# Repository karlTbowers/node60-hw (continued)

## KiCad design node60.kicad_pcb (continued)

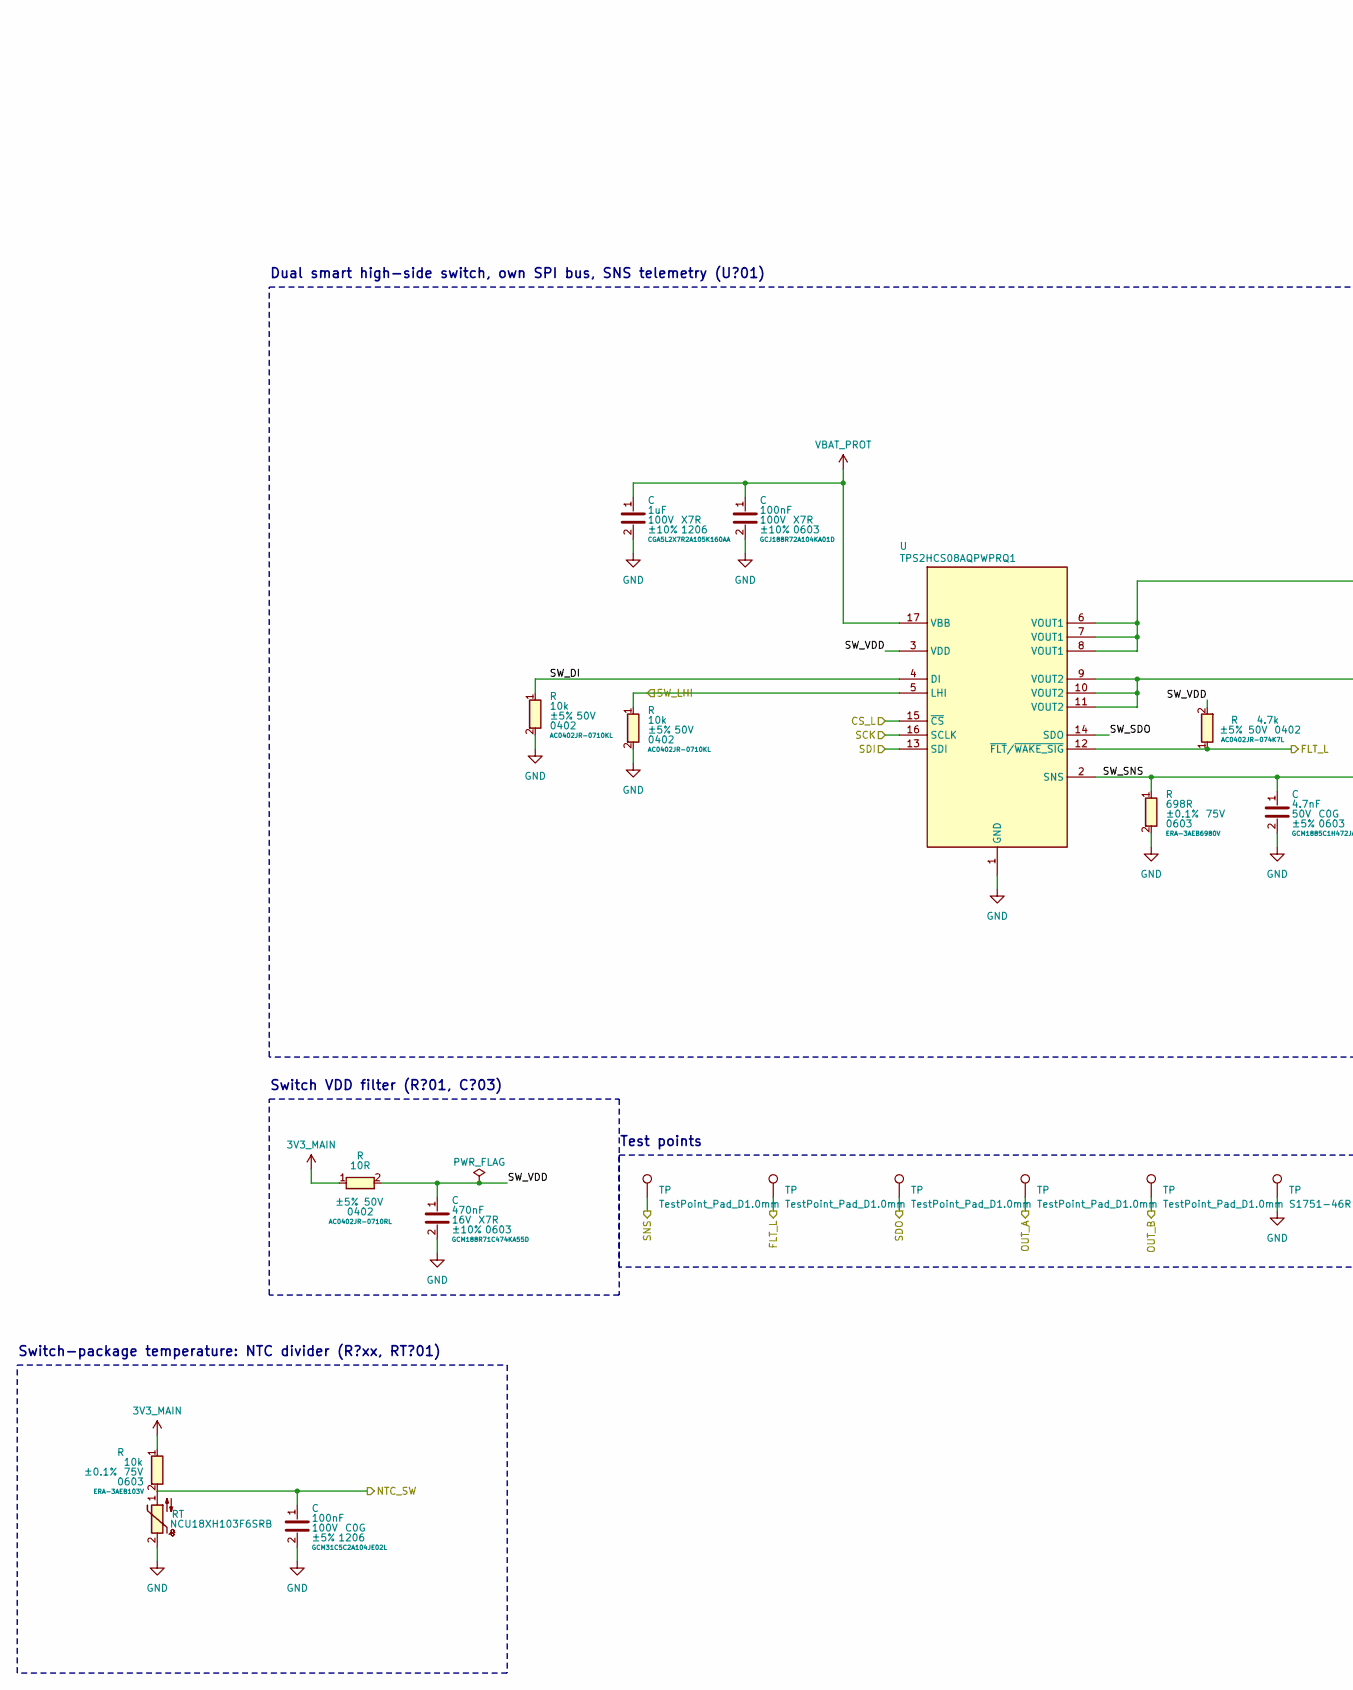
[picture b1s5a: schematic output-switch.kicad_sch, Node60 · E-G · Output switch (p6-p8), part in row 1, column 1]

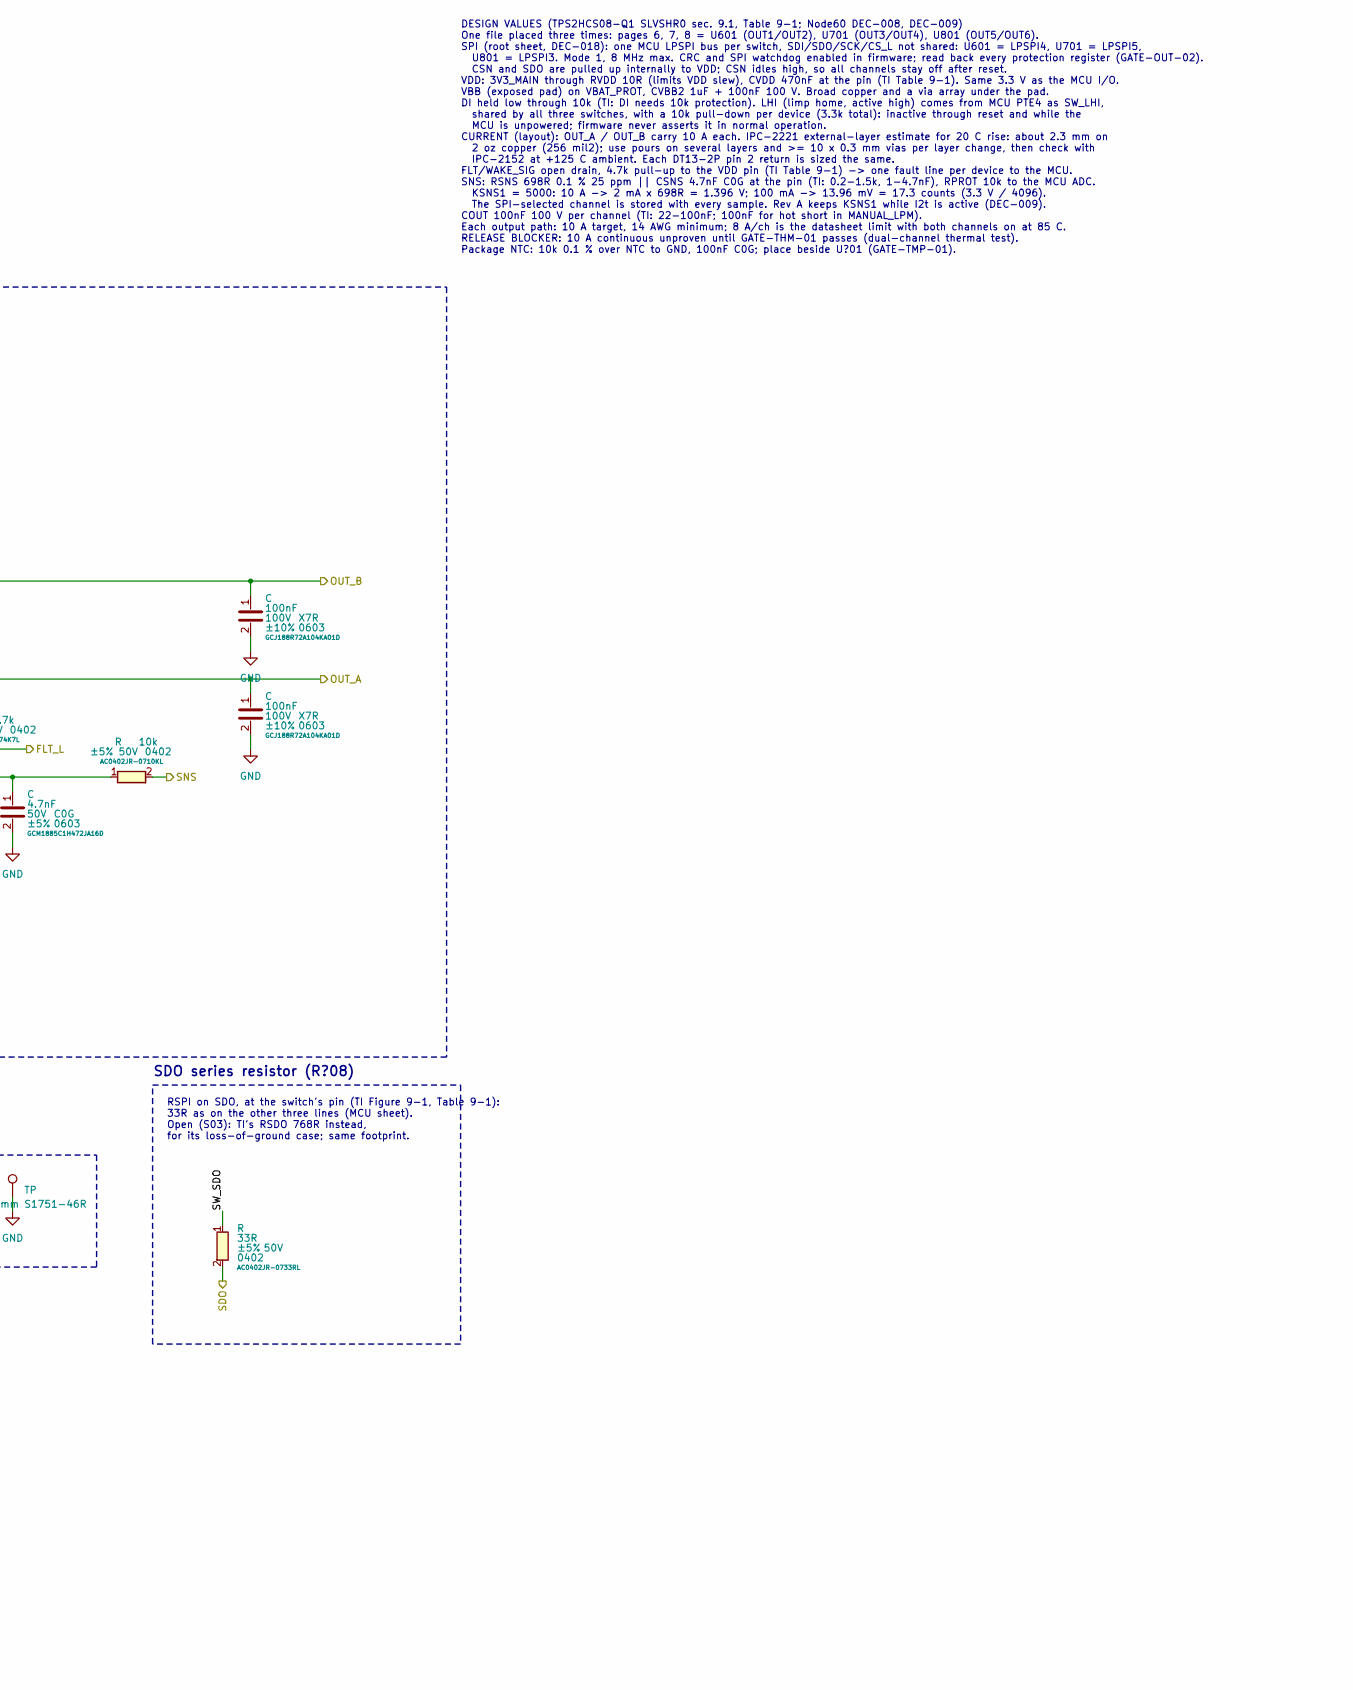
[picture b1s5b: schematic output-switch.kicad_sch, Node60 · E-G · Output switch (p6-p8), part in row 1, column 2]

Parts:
C: 100nF; C_0603_1608Metric; Voltage 100V; Tolerance ±10%; MPN GCJ188R72A104KA01D; DigiKey_PN 490-13420-1-ND
R: 10R; R_0402_1005Metric; Tolerance ±5%; Voltage 50V; MPN AC0402JR-0710RL; DigiKey_PN YAG3519CT-ND
RT: NCU18XH103F6SRB; R_NTC_0603_1608Metric_Pad0.7x0.7mm; MPN NCU18XH103F6SRB; DigiKey_PN 490-18139-1-ND
TP: TestPoint_Pad_D1.0mm; MPN TestPoint_Pad_D1.0mm
U: TPS2HCS08AQPWPRQ1; HTSSOP-16-1EP_4.4x5mm_P0.65mm_EP3.4x5mm_Mask2.78x3.313mm; MPN TPS2HCS08AQPWPRQ1; DigiKey_PN 296-TPS2HCS08AQPWPRQ1CT-ND

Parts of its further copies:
C601, C605, C606, C607, C701, C705, C706, C707, C801, C805, C806, C807: 100nF; C_0603_1608Metric; Voltage 100V; Tolerance ±10%; MPN GCJ188R72A104KA01D; DigiKey_PN 490-13420-1-ND
R601, R701, R801: 10R; R_0402_1005Metric; Tolerance ±5%; Voltage 50V; MPN AC0402JR-0710RL; DigiKey_PN YAG3519CT-ND
RT601, RT701, RT801: NCU18XH103F6SRB; R_NTC_0603_1608Metric_Pad0.7x0.7mm; MPN NCU18XH103F6SRB; DigiKey_PN 490-18139-1-ND
TP601, TP602, TP603, TP604, TP605, TP701, TP702, TP703, TP704, TP705, TP801, TP802, TP803, TP804, TP805: TestPoint_Pad_D1.0mm; MPN TestPoint_Pad_D1.0mm
U601, U701, U801: TPS2HCS08AQPWPRQ1; HTSSOP-16-1EP_4.4x5mm_P0.65mm_EP3.4x5mm_Mask2.78x3.313mm; MPN TPS2HCS08AQPWPRQ1; DigiKey_PN 296-TPS2HCS08AQPWPRQ1CT-ND

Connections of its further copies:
3V3_MAIN: R601.1, R701.1, R801.1; also elsewhere on the board
/NTC_SW1: C607.1, RT601.1; also elsewhere on the board
/NTC_SW2: C707.1, RT701.1; also elsewhere on the board
/NTC_SW3: C807.1, RT801.1; also elsewhere on the board
/OUT1: C606.1, TP604.1 (1_1), U601.9 (VOUT2), U601.10 (VOUT2), U601.11 (VOUT2); also elsewhere on the board
/OUT2: C605.1, TP605.1 (1_1), U601.6 (VOUT1), U601.7 (VOUT1), U601.8 (VOUT1); also elsewhere on the board
/OUT3: C706.1, TP704.1 (1_1), U701.9 (VOUT2), U701.10 (VOUT2), U701.11 (VOUT2); also elsewhere on the board
/OUT4: C705.1, TP705.1 (1_1), U701.6 (VOUT1), U701.7 (VOUT1), U701.8 (VOUT1); also elsewhere on the board
/OUT5: C806.1, TP804.1 (1_1), U801.9 (VOUT2), U801.10 (VOUT2), U801.11 (VOUT2); also elsewhere on the board
/OUT6: C805.1, TP805.1 (1_1), U801.6 (VOUT1), U801.7 (VOUT1), U801.8 (VOUT1); also elsewhere on the board
/Outputs 1-2/SW_DI: U601.4 (DI); also elsewhere on the board
/Outputs 1-2/SW_SDO: U601.14 (SDO); also elsewhere on the board
/Outputs 1-2/SW_SNS: U601.2 (SNS); also elsewhere on the board
/Outputs 1-2/SW_VDD: R601.2, U601.3 (VDD); also elsewhere on the board
/Outputs 3-4/SW_DI: U701.4 (DI); also elsewhere on the board
/Outputs 3-4/SW_SDO: U701.14 (SDO); also elsewhere on the board
/Outputs 3-4/SW_SNS: U701.2 (SNS); also elsewhere on the board
/Outputs 3-4/SW_VDD: R701.2, U701.3 (VDD); also elsewhere on the board
/Outputs 5-6/SW_DI: U801.4 (DI); also elsewhere on the board
/Outputs 5-6/SW_SDO: U801.14 (SDO); also elsewhere on the board
/Outputs 5-6/SW_SNS: U801.2 (SNS); also elsewhere on the board
/Outputs 5-6/SW_VDD: R801.2, U801.3 (VDD); also elsewhere on the board
/SPI3_SWITCH3_CS_L: U801.15 (~CS); also elsewhere on the board
/SPI3_SWITCH3_MISO: TP803.1 (1_1); also elsewhere on the board
/SPI3_SWITCH3_MOSI: U801.13 (SDI); also elsewhere on the board
/SPI3_SWITCH3_SCK: U801.16 (SCLK); also elsewhere on the board
/SPI4_SWITCH1_CS_L: U601.15 (~CS); also elsewhere on the board
/SPI4_SWITCH1_MISO: TP603.1 (1_1); also elsewhere on the board
/SPI4_SWITCH1_MOSI: U601.13 (SDI); also elsewhere on the board
/SPI4_SWITCH1_SCK: U601.16 (SCLK); also elsewhere on the board
/SPI5_SWITCH2_CS_L: U701.15 (~CS); also elsewhere on the board
/SPI5_SWITCH2_MISO: TP703.1 (1_1); also elsewhere on the board
/SPI5_SWITCH2_MOSI: U701.13 (SDI); also elsewhere on the board
/SPI5_SWITCH2_SCK: U701.16 (SCLK); also elsewhere on the board
/SW1_FLT_L: TP602.1 (1_1), U601.12 (~FLT/~WAKE_SIG); also elsewhere on the board
/SW1_SNS: TP601.1 (1_1); also elsewhere on the board
/SW2_FLT_L: TP702.1 (1_1), U701.12 (~FLT/~WAKE_SIG); also elsewhere on the board
/SW2_SNS: TP701.1 (1_1); also elsewhere on the board
/SW3_FLT_L: TP802.1 (1_1), U801.12 (~FLT/~WAKE_SIG); also elsewhere on the board
/SW3_SNS: TP801.1 (1_1); also elsewhere on the board
/SW_LHI: U601.5 (LHI), U701.5 (LHI), U801.5 (LHI); also elsewhere on the board
GND: C601.2, C605.2, C606.2, C607.2, C701.2, C705.2, C706.2, C707.2, C801.2, C805.2, C806.2, C807.2, RT601.2, RT701.2, RT801.2, U601.1 (GND), U701.1 (GND), U801.1 (GND); also elsewhere on the board
VBAT_PROT: C601.1, C701.1, C801.1, U601.17 (VBB), U701.17 (VBB), U801.17 (VBB); also elsewhere on the board

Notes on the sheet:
Dual smart high-side switch, own SPI bus, SNS telemetry (U?01)
Switch VDD filter (R?01, C?03)
Switch-package temperature: NTC divider (R?xx, RT?01)
Test points
DESIGN VALUES (TPS2HCS08-Q1 SLVSHR0 sec. 9.1, Table 9-1; Node60 DEC-008, DEC-009) One file placed three times: pages 6, 7, 8 = U601 (OUT1/OUT2), U701 (OUT3/OUT4), U801 (OUT5/OUT6). SPI (root sheet, DEC-018): one MCU LPSPI bus per switch, SDI/SDO/SCK/CS_L not shared: U601 = LPSPI4, U701 = LPSPI5, U8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
SDO series resistor (R?08)
RSPI on SDO, at the switch's pin (TI Figure 9-1, Table 9-1): 33R as on the other three lines (MCU sheet). Open (S03): TI's RSDO 768R instead, for its loss-of-ground case; same footprint.

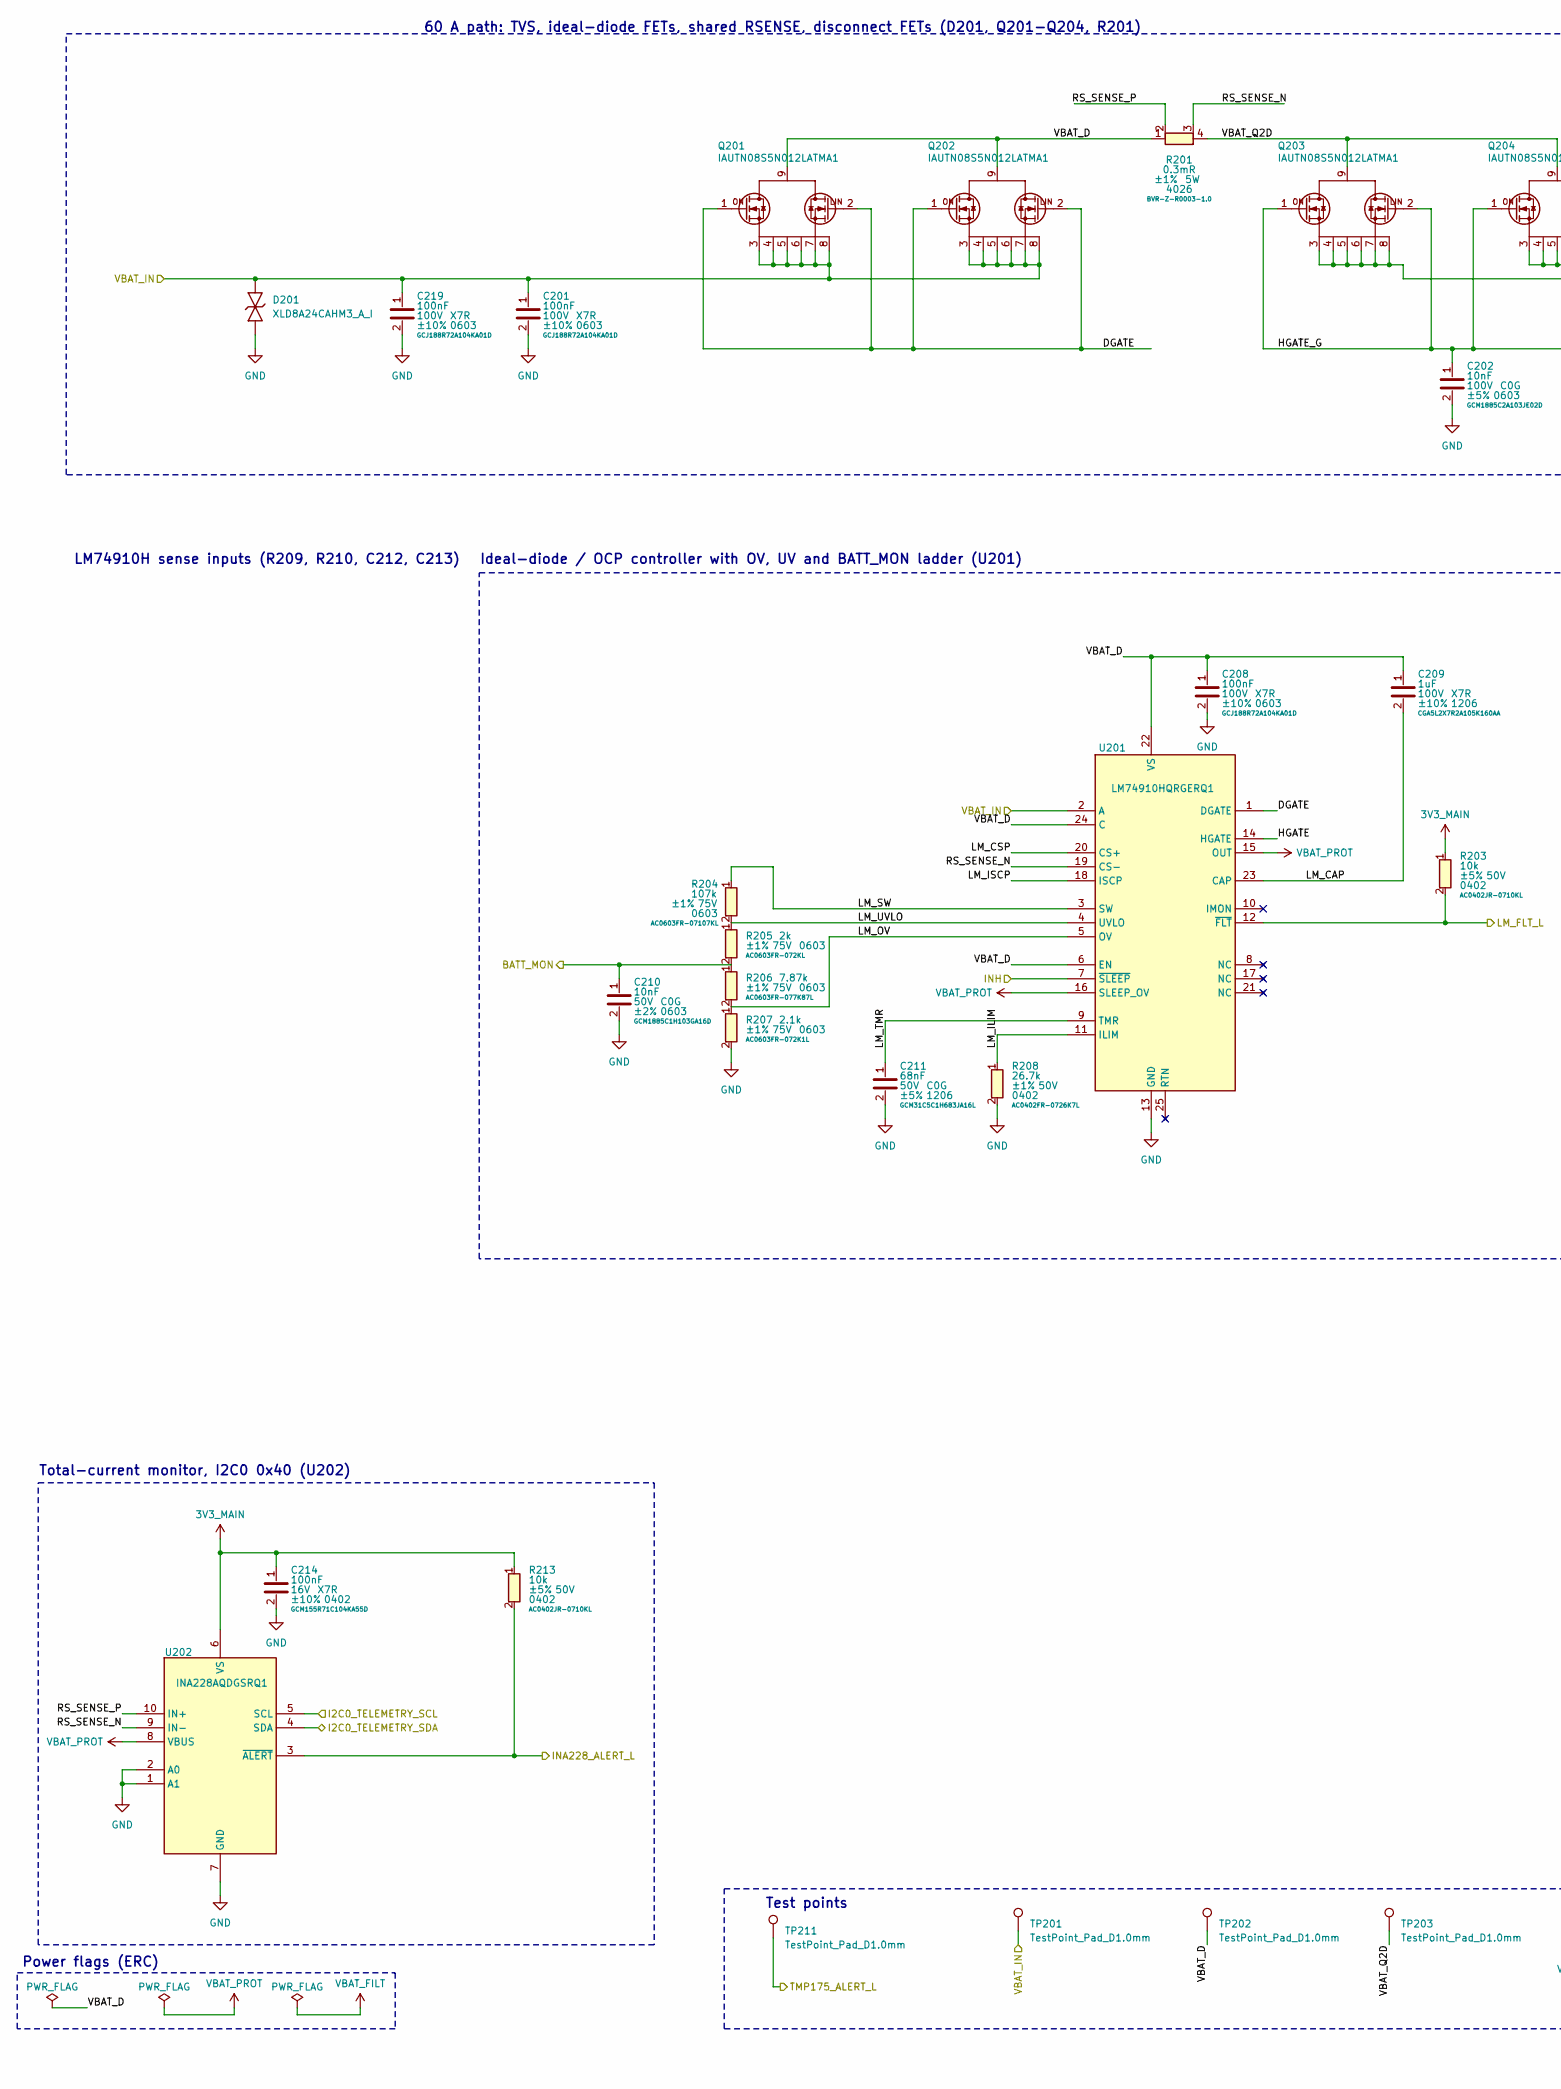
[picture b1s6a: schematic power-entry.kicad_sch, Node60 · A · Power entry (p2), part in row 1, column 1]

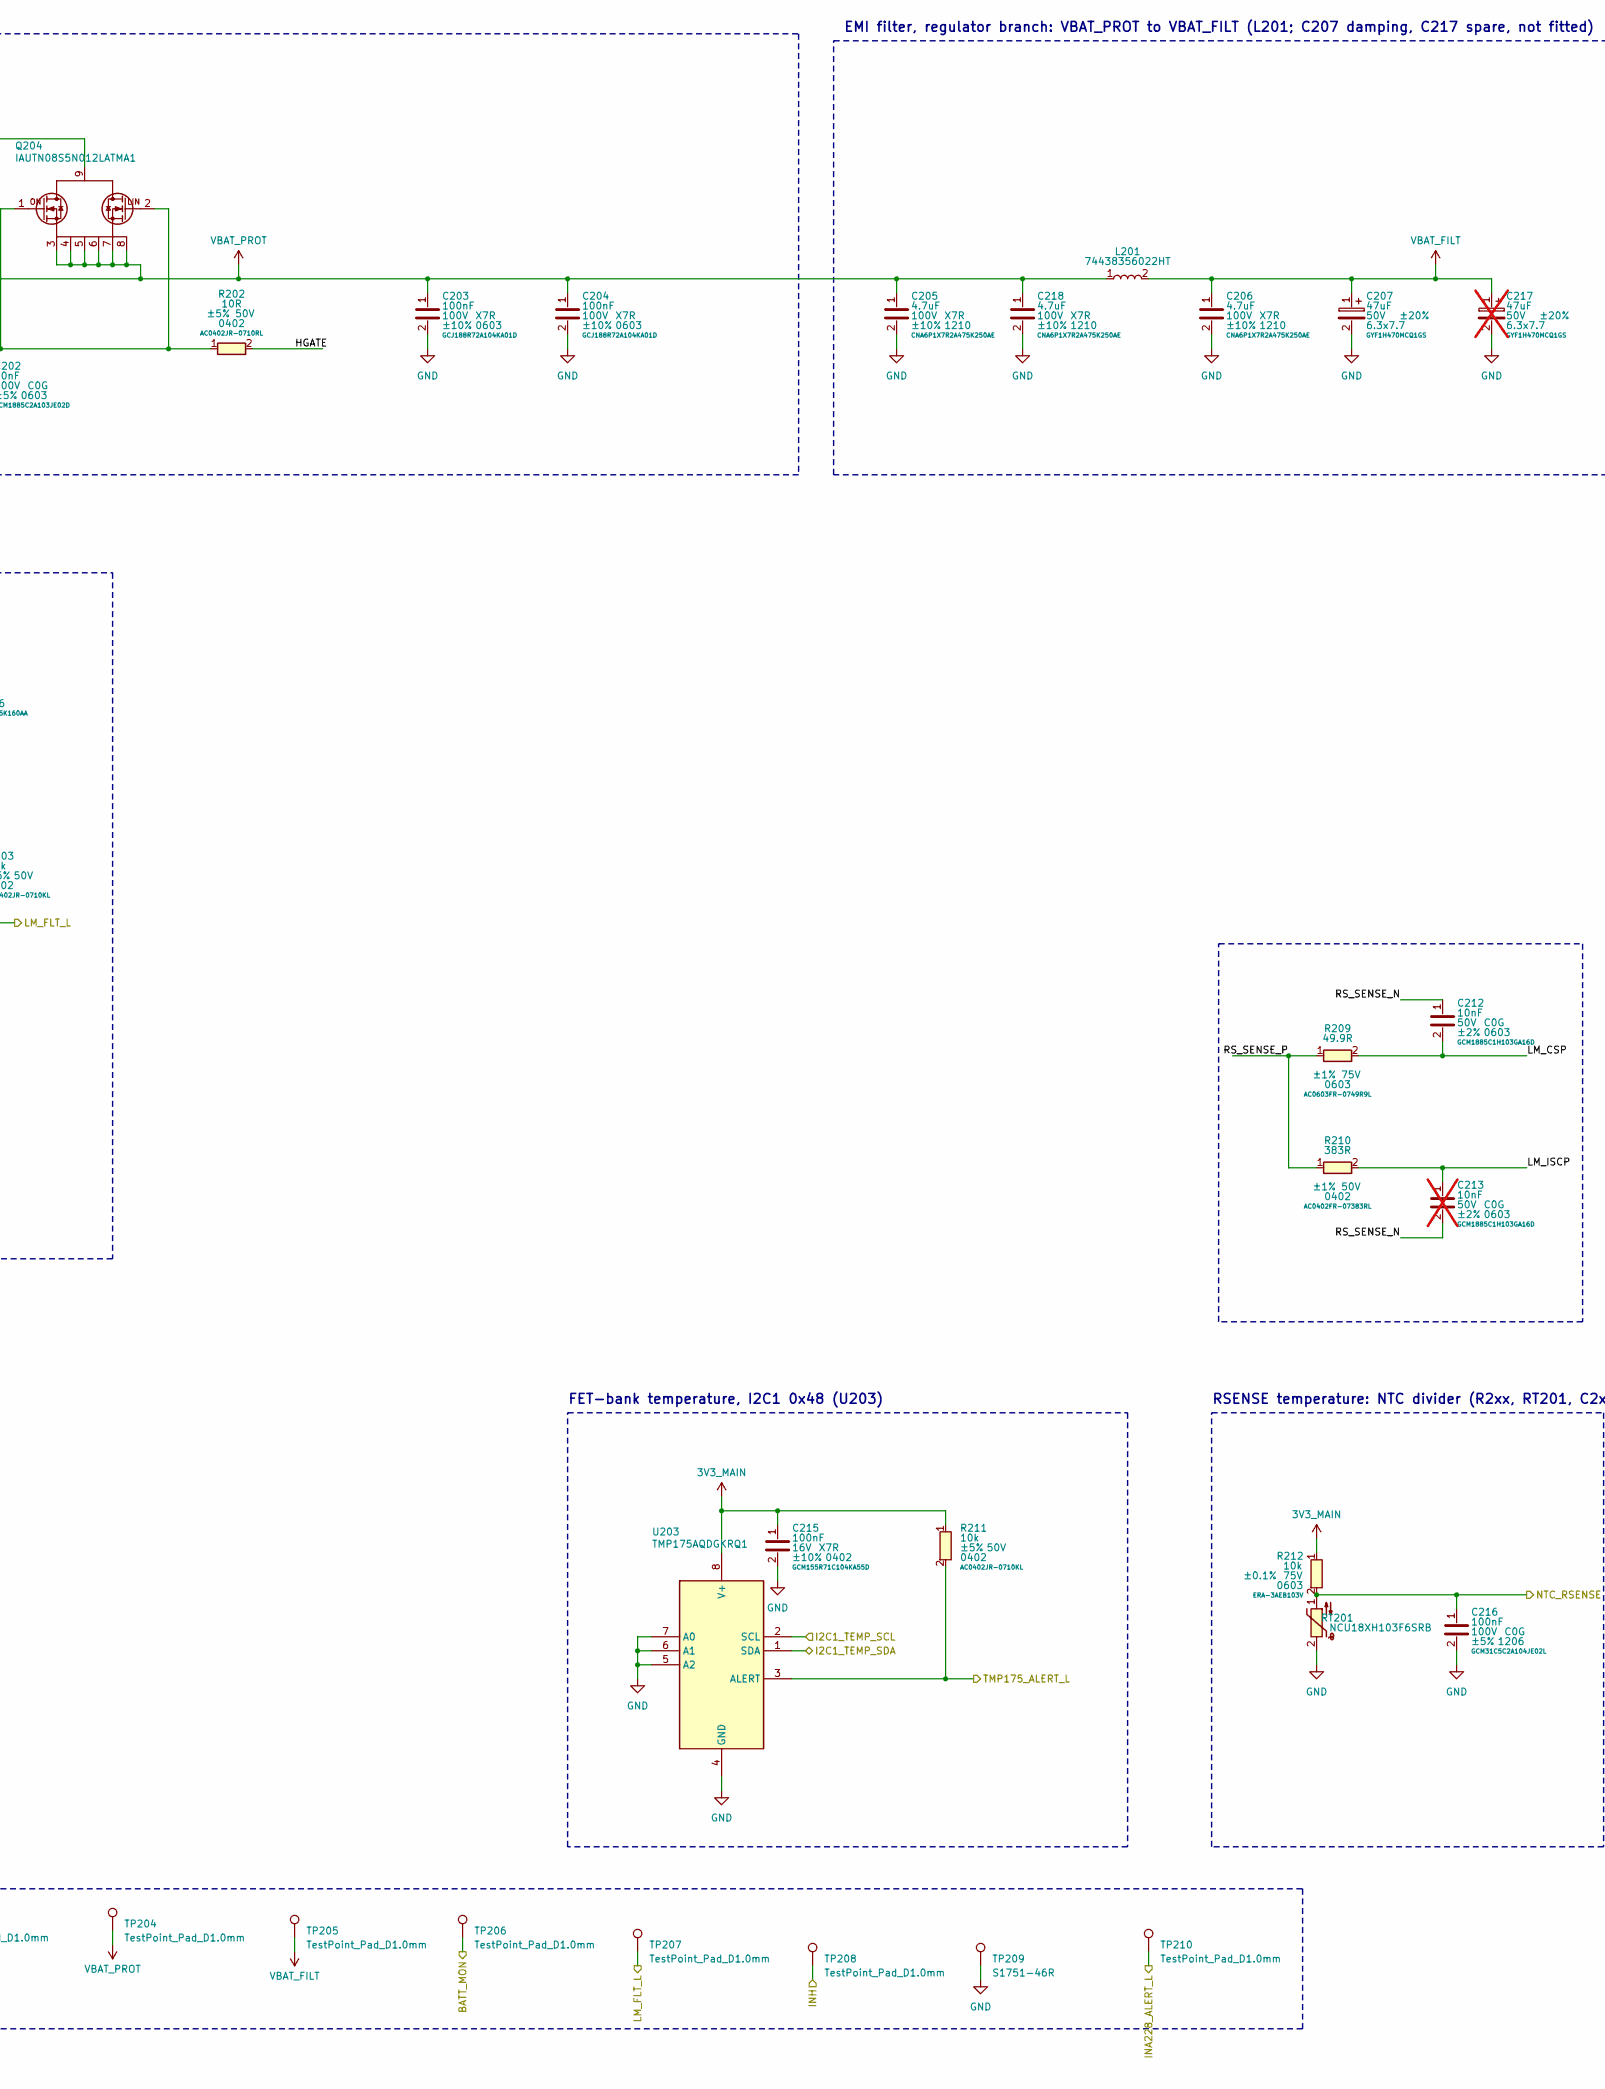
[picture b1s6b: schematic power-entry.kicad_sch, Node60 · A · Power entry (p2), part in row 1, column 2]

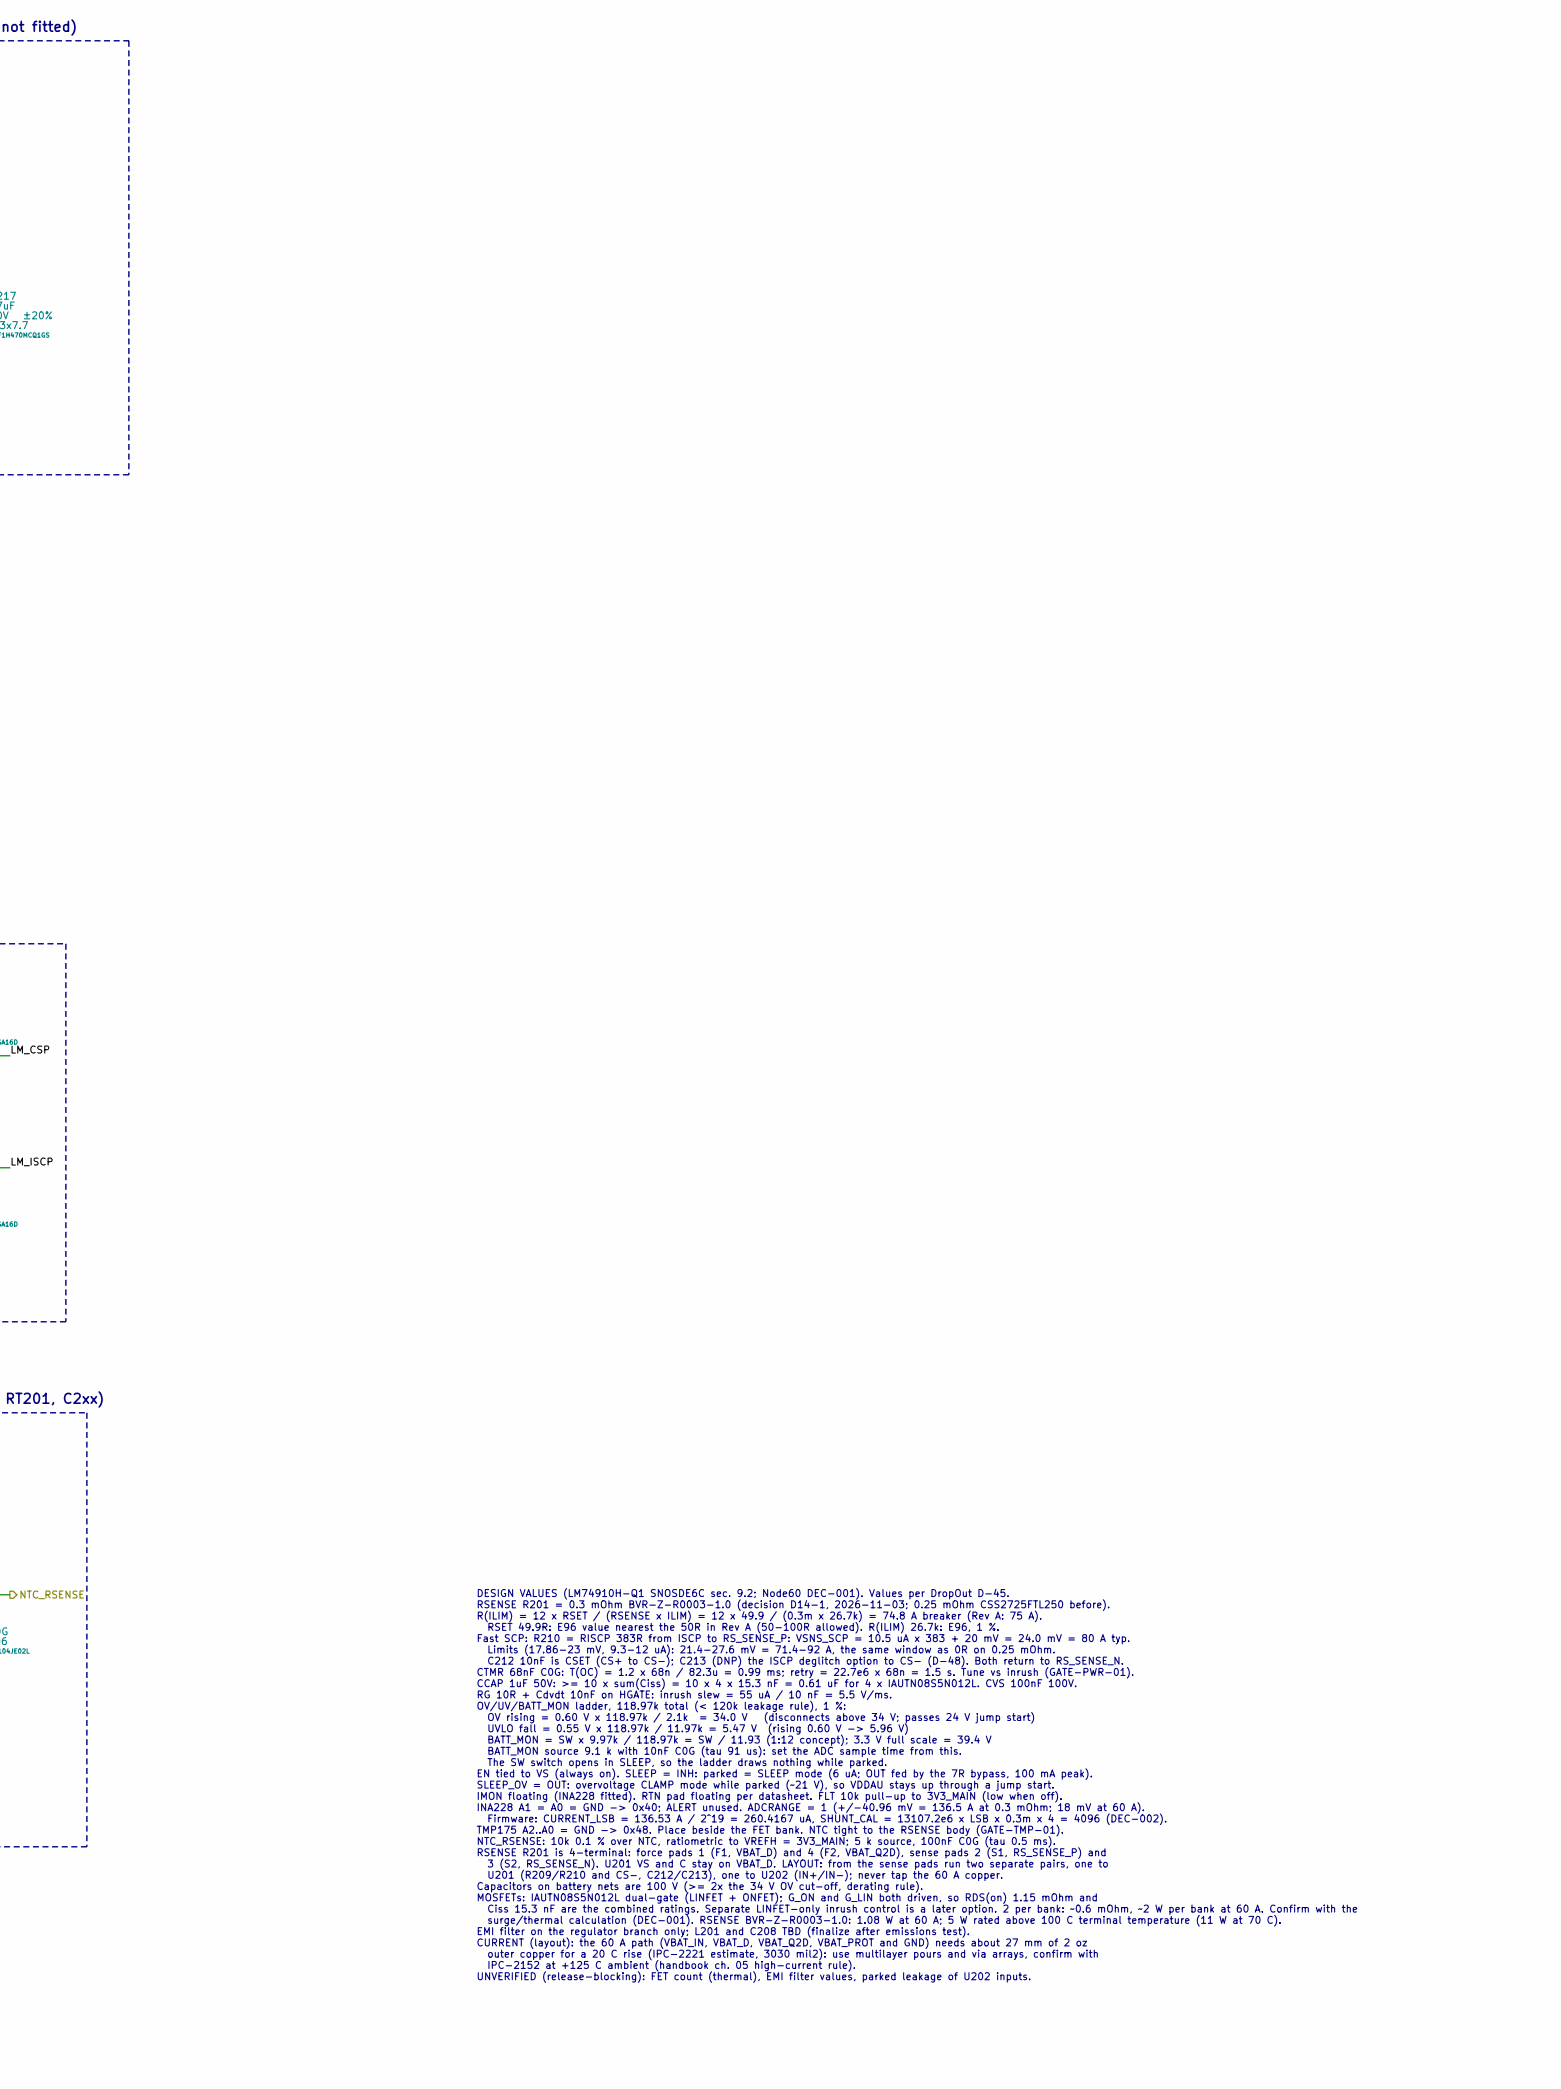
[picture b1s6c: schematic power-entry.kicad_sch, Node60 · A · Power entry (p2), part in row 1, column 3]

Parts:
C201, C203, C204, C208, C219: 100nF; C_0603_1608Metric; Voltage 100V; Tolerance ±10%; MPN GCJ188R72A104KA01D; DigiKey_PN 490-13420-1-ND
C202: 10nF; C_0603_1608Metric; Voltage 100V; Tolerance ±5%; MPN GCM1885C2A103JE02D; DigiKey_PN 490-GCM1885C2A103JE02DCT-ND
C205, C206, C218: 4.7uF; C_1210_3225Metric; Voltage 100V; Tolerance ±10%; MPN CNA6P1X7R2A475K250AE; DigiKey_PN 445-181409-1-ND
C207: 47uF; CP_Elec_6.3x7.7; Voltage 50V; Tolerance ±20%; MPN GYF1H470MCQ1GS; DigiKey_PN GYF1H470MCQ1GCT-ND
C209: 1uF; C_1206_3216Metric; Voltage 100V; Tolerance ±10%; MPN CGA5L2X7R2A105K160AA; DigiKey_PN 445-5845-1-ND
C210, C212: 10nF; C_0603_1608Metric; Voltage 50V; Tolerance ±2%; MPN GCM1885C1H103GA16D; DigiKey_PN 490-GCM1885C1H103GA16DCT-ND
C211: 68nF; C_1206_3216Metric; Voltage 50V; Tolerance ±5%; MPN GCM31C5C1H683JA16L; DigiKey_PN 490-5323-1-ND
C213: 10nF; C_0603_1608Metric; Voltage 50V; Tolerance ±2%; MPN GCM1885C1H103GA16D; DigiKey_PN 490-GCM1885C1H103GA16DCT-ND; not fitted
C214, C215: 100nF; C_0402_1005Metric; Voltage 16V; Tolerance ±10%; MPN GCM155R71C104KA55D; DigiKey_PN 490-4759-1-ND
C216: 100nF; C_1206_3216Metric; Voltage 100V; Tolerance ±5%; MPN GCM31C5C2A104JE02L; DigiKey_PN 490-GCM31C5C2A104JE02LCT-ND
C217: 47uF; CP_Elec_6.3x7.7; Voltage 50V; Tolerance ±20%; MPN GYF1H470MCQ1GS; DigiKey_PN GYF1H470MCQ1GCT-ND; not fitted
D201: XLD8A24CAHM3_A_I; D_DO-218AC; MPN XLD8A24CAHM3_A/I; DigiKey_PN 112-XLD8A24CAHM3_A/ICT-ND
L201: 74438356022HT; L_Wuerth_MAPI-4020; MPN 74438356022HT; DigiKey_PN 732-74438356022HTCT-ND
Q201, Q202, Q203, Q204: IAUTN08S5N012LATMA1; Infineon_PG-HSOF-8-2; MPN IAUTN08S5N012LATMA1; DigiKey_PN 448-IAUTN08S5N012LATMA1CT-ND
R201: BVR-Z-R0003-1.0; R_Shunt_Isabellenhuette_BVR4026; Tolerance ±1%; MPN BVR-Z-R0003-1.0; DigiKey_PN 4423-BVR-Z-R0003-1.0CT-ND
R202: 10R; R_0402_1005Metric; Tolerance ±5%; Voltage 50V; MPN AC0402JR-0710RL; DigiKey_PN YAG3519CT-ND
R203, R211, R213: 10k; R_0402_1005Metric; Tolerance ±5%; Voltage 50V; MPN AC0402JR-0710KL; DigiKey_PN YAG3517CT-ND
R204: 107k; R_0603_1608Metric; Tolerance ±1%; Voltage 75V; MPN AC0603FR-07107KL; DigiKey_PN 13-AC0603FR-07107KLCT-ND
R205: 2k; R_0603_1608Metric; Tolerance ±1%; Voltage 75V; MPN AC0603FR-072KL; DigiKey_PN YAG3590CT-ND
R206: 7.87k; R_0603_1608Metric; Tolerance ±1%; Voltage 75V; MPN AC0603FR-077K87L; DigiKey_PN 13-AC0603FR-077K87LCT-ND
R207: 2.1k; R_0603_1608Metric; Tolerance ±1%; Voltage 75V; MPN AC0603FR-072K1L; DigiKey_PN 13-AC0603FR-072K1LCT-ND
R208: 26.7k; R_0402_1005Metric; Tolerance ±1%; Voltage 50V; MPN AC0402FR-0726K7L; DigiKey_PN YAG5658CT-ND
R209: 49.9R; R_0603_1608Metric; Tolerance ±1%; Voltage 75V; MPN AC0603FR-0749R9L; DigiKey_PN YAG3611CT-ND
R210: 383R; R_0402_1005Metric; Tolerance ±1%; Voltage 50V; MPN AC0402FR-07383RL; DigiKey_PN AC0402FR-07383RL-ND
R212: 10k; R_0603_1608Metric; Tolerance ±0.1%; Voltage 75V; MPN ERA-3AEB103V; DigiKey_PN P10KDBCT-ND
RT201: NCU18XH103F6SRB; R_NTC_0603_1608Metric_Pad0.7x0.7mm; MPN NCU18XH103F6SRB; DigiKey_PN 490-18139-1-ND
TP201, TP202, TP203, TP204, TP205, TP206, TP207, TP208, TP210, TP211: TestPoint_Pad_D1.0mm; MPN TestPoint_Pad_D1.0mm
TP209: S1751-46R; TestPoint_Harwin_S1751; MPN S1751-46R; DigiKey_PN 952-1478-1-ND
U201: LM74910HQRGERQ1; Texas_RGE0024T_VQFN-24-1EP_4x4mm_P0.5mm_EP2.1x2.1mm; MPN LM74910HQRGERQ1; DigiKey_PN 296-LM74910HQRGERQ1CT-ND
U202: INA228AQDGSRQ1; Texas_DGS0010A_TSSOP-10_3x3mm_P0.5mm; MPN INA228AQDGSRQ1; DigiKey_PN 296-INA228AQDGSRQ1CT-ND
U203: TMP175AQDGKRQ1; Texas_DGK0008A_TSSOP-8_3x3mm_P0.65mm; MPN TMP175AQDGKRQ1; DigiKey_PN 296-48992-1-ND

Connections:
3V3_MAIN: C214.1, C215.1, R203.1, R211.1, R212.1, R213.1, U202.6 (VS), U203.8 (V+); also elsewhere on the board
/BATT_MON: C210.1, R205.2, R206.1, TP206.1 (1_1); also elsewhere on the board
/I2C0_TELEMETRY_SCL: U202.5 (SCL); also elsewhere on the board
/I2C0_TELEMETRY_SDA: U202.4 (SDA); also elsewhere on the board
/I2C1_TEMP_SCL: U203.2 (SCL); also elsewhere on the board
/I2C1_TEMP_SDA: U203.1 (SDA); also elsewhere on the board
/INA228_ALERT_L: R213.2, TP210.1 (1_1), U202.3 (~ALERT); also elsewhere on the board
/INH: TP208.1 (1_1), U201.7 (~SLEEP); also elsewhere on the board
/LM_FLT_L: R203.2, TP207.1 (1_1), U201.12 (~FLT); also elsewhere on the board
/NTC_RSENSE: C216.1, R212.2, RT201.1; also elsewhere on the board
/Power entry/DGATE: Q201.1 (G_ON), Q201.2 (G_LIN), Q202.1 (G_ON), Q202.2 (G_LIN), U201.1 (DGATE)
/Power entry/HGATE: R202.2, U201.14 (HGATE)
/Power entry/HGATE_G: C202.1, Q203.1 (G_ON), Q203.2 (G_LIN), Q204.1 (G_ON), Q204.2 (G_LIN), R202.1
/Power entry/LM_CAP: C209.2, U201.23 (CAP)
/Power entry/LM_CSP: C212.2, R209.2, U201.20 (CS+)
/Power entry/LM_ILIM: R208.1, U201.11 (ILIM)
/Power entry/LM_ISCP: C213.1, R210.2, U201.18 (ISCP)
/Power entry/LM_OV: R206.2, R207.1, U201.5 (OV)
/Power entry/LM_SW: R204.1, U201.3 (SW)
/Power entry/LM_TMR: C211.1, U201.9 (TMR)
/Power entry/LM_UVLO: R204.2, R205.1, U201.4 (UVLO)
/Power entry/RS_SENSE_N: C212.1, C213.2, R201.3 (S2), U201.19 (CS-), U202.9 (IN-)
/Power entry/RS_SENSE_P: R201.2 (S1), R209.1, R210.1, U202.10 (IN+)
/Power entry/VBAT_D: C208.1, C209.1, Q201.9 (D), Q202.9 (D), R201.1 (F1), TP202.1 (1_1), U201.6 (EN), U201.22 (VS), U201.24 (C)
/Power entry/VBAT_Q2D: Q203.9 (D), Q204.9 (D), R201.4 (F2), TP203.1 (1_1)
/TMP175_ALERT_L: R211.2, TP211.1 (1_1), U203.3 (ALERT); also elsewhere on the board
/VBAT_IN: C201.1, C219.1, D201.2 (A2), Q201.3 (S), Q201.4 (S), Q201.5 (S), Q201.6 (S), Q201.7 (S), Q201.8 (S), Q202.3 (S), Q202.4 (S), Q202.5 (S), Q202.6 (S), Q202.7 (S), Q202.8 (S), TP201.1 (1_1), U201.2 (A); also elsewhere on the board
GND: C201.2, C202.2, C203.2, C204.2, C205.2, C206.2, C207.2, C208.2, C210.2, C211.2, C214.2, C215.2, C216.2, C217.2, C218.2, C219.2, D201.1 (A1), R207.2, R208.2, RT201.2, TP209.1 (1_1), U201.13 (GND), U202.1 (A1), U202.2 (A0), U202.7 (GND), U203.4 (GND), U203.5 (A2), U203.6 (A1), U203.7 (A0); also elsewhere on the board
VBAT_FILT: C206.1, C207.1, C217.1, L201.2, TP205.1 (1_1); also elsewhere on the board
VBAT_PROT: C203.1, C204.1, C205.1, C218.1, L201.1, Q203.3 (S), Q203.4 (S), Q203.5 (S), Q203.6 (S), Q203.7 (S), Q203.8 (S), Q204.3 (S), Q204.4 (S), Q204.5 (S), Q204.6 (S), Q204.7 (S), Q204.8 (S), TP204.1 (1_1), U201.15 (OUT), U201.16 (SLEEP_OV), U202.8 (VBUS); also elsewhere on the board

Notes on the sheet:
Total-current monitor, I2C0 0x40 (U202)
LM74910H sense inputs (R209, R210, C212, C213)
EMI filter, regulator branch: VBAT_PROT to VBAT_FILT (L201; C207 damping, C217 spare, not fitted)
FET-bank temperature, I2C1 0x48 (U203)
Power flags (ERC)
60 A path: TVS, ideal-diode FETs, shared RSENSE, disconnect FETs (D201, Q201-Q204, R201)
Ideal-diode / OCP controller with OV, UV and BATT_MON ladder (U201)
Test points
RSENSE temperature: NTC divider (R2xx, RT201, C2xx)
DESIGN VALUES (LM74910H-Q1 SNOSDE6C sec. 9.2; Node60 DEC-001). Values per DropOut D-45. RSENSE R201 = 0.3 mOhm BVR-Z-R0003-1.0 (decision D14-1, 2026-11-03; 0.25 mOhm CSS2725FTL250 before). R(ILIM) = 12 x RSET / (RSENSE x ILIM) = 12 x 49.9 / (0.3m x 26.7k) = 74.8 A breaker (Rev A: 75 A). RSET 49.9R: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
